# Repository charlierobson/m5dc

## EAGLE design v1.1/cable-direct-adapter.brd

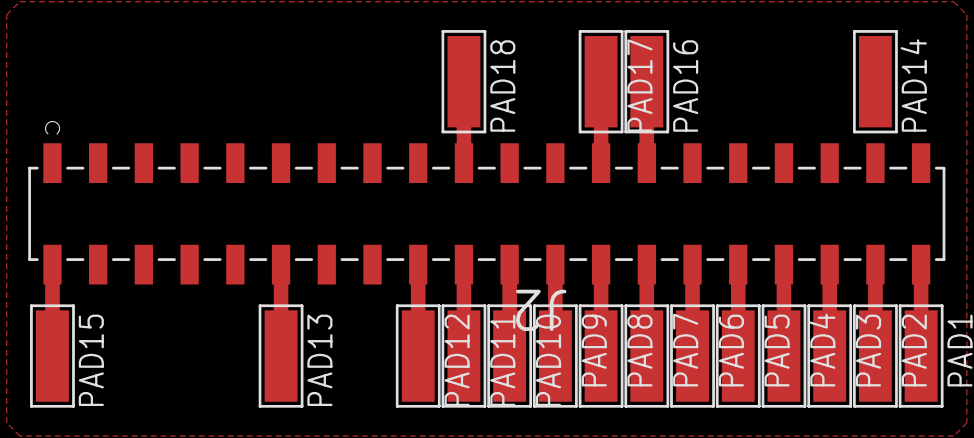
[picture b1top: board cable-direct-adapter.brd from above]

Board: 2 copper layers, 19 parts (0 on the bottom side), 18 nets.

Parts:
J2: SSM-120-L-DV; SAMTEC_SSM-120-L-DV
PAD1, PAD2, PAD3, PAD4, PAD5, PAD6, PAD7, PAD8, PAD9, PAD10, PAD11, PAD12, PAD13, PAD14, PAD15, PAD16, PAD17, PAD18: WIREPADSMD5-1,8; 5-1,8

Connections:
!IN: J2.19, PAD18.1
!OUT: J2.12, PAD13.1
!RESET: J2.2, PAD15.1
A0: J2.25, PAD17.1
A1: J2.27, PAD16.1
A2: J2.40, PAD1.1
A3: J2.34, PAD4.1
A6: J2.38, PAD2.1
A7: J2.36, PAD3.1
D0: J2.30, PAD6.1
D1: J2.22, PAD10.1
D2: J2.32, PAD5.1
D3: J2.26, PAD8.1
D4: J2.18, PAD12.1
D5: J2.28, PAD7.1
D6: J2.24, PAD9.1
D7: J2.20, PAD11.1
GND: J2.8, J2.29, J2.37, PAD14.1

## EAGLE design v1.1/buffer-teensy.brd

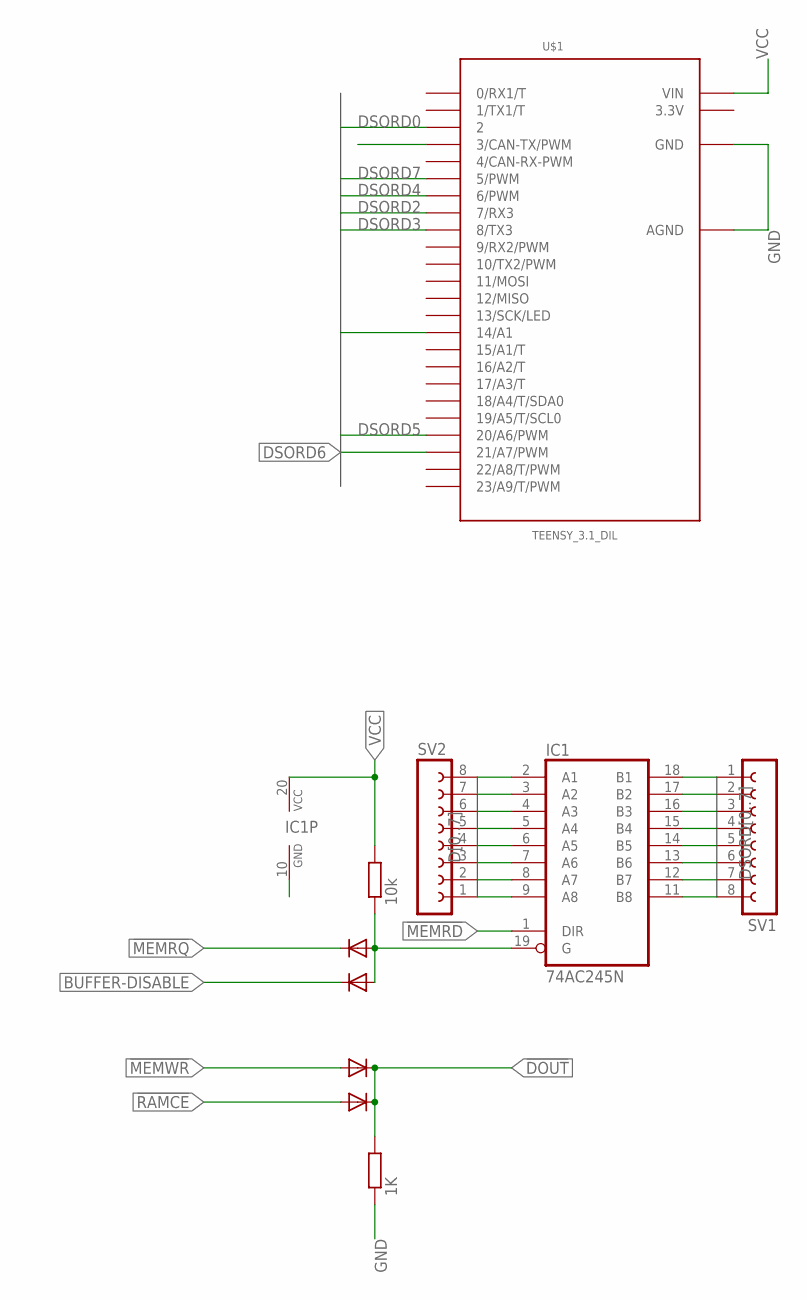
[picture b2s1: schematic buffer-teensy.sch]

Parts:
D1, D2, D3, D4: 1N4148DO35-7; DO35-7
IC1: 74AC245N; DIL20
R1: 10k; 0204/7
R2: 1K; 0204/7
SV1, SV2: FE08-1; FE08
U$1: TEENSY_3.1_DIL; TEENSY3-DIL

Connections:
3.3V: U$1.3.3V
!DOUT: D3.C, D4.C, R2.2, U$1.3 (3/CAN-TX/PWM)
!MEMRD: IC1.1 (DIR)
!MEMRQ: D1.C
!MEMWR: D3.A
!RAMCE: D4.A
BUFFER-DISABLE: D2.C
D0: IC1.2 (A1), SV2.8
D1: IC1.3 (A2), SV2.7
D2: IC1.4 (A3), SV2.6
D3: IC1.5 (A4), SV2.5
D4: IC1.6 (A5), SV2.4
D5: IC1.7 (A6), SV2.3
D6: IC1.8 (A7), SV2.2
D7: IC1.9 (A8), SV2.1
DSORD0: IC1.18 (B1), SV1.1, U$1.2
DSORD1: IC1.17 (B2), SV1.2, U$1.14/A0 (14/A1)
DSORD2: IC1.16 (B3), SV1.3, U$1.7 (7/RX3)
DSORD3: IC1.15 (B4), SV1.4, U$1.8 (8/TX3)
DSORD4: IC1.14 (B5), SV1.5, U$1.6 (6/PWM)
DSORD5: IC1.13 (B6), SV1.6, U$1.20/A6 (20/A6/PWM)
DSORD6: IC1.12 (B7), SV1.7, U$1.21/A7 (21/A7/PWM)
DSORD7: IC1.11 (B8), SV1.8, U$1.5 (5/PWM)
GND: IC1.10 (GND), R2.1, U$1.AGND, U$1.GND
unnamed: D1.A, D2.A, IC1.19 (G), R1.1
VCC: IC1.20 (VCC), R1.2, U$1.VIN

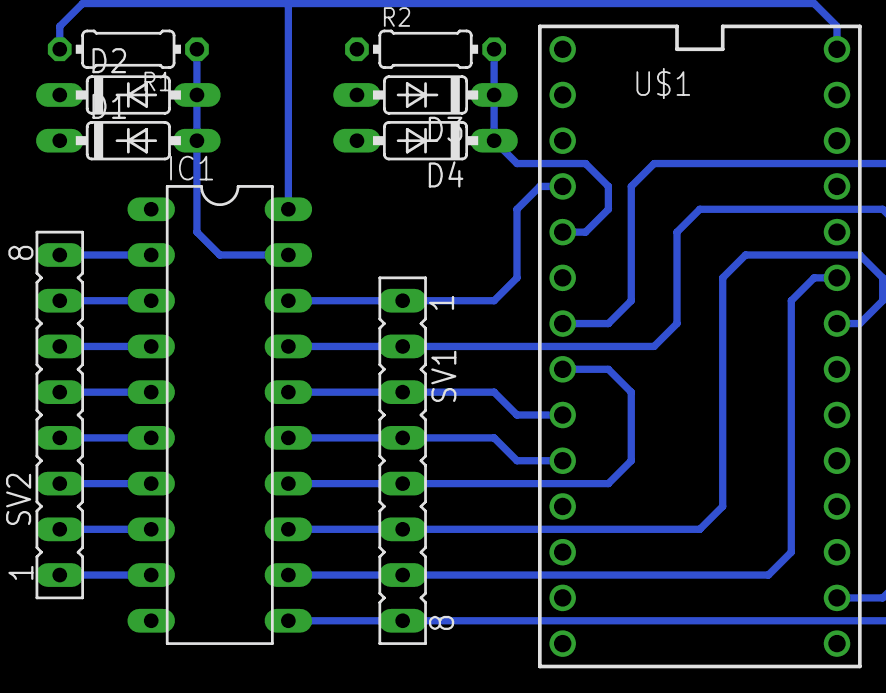
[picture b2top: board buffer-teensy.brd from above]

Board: 2 copper layers, 10 parts (0 on the bottom side), 20 nets.

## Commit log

2016-09-30 create new repo
2016-09-30 update test rom to load a file from an einsdein
2016-09-30 add direct adapter
2016-10-01 add xilinx code and finish direct adapter
2016-10-03 add new functinos to test rom
2016-10-03 add test mode
2016-10-04 add pic code to project
2016-10-04 add cpld and update rom to be mostly working
2016-10-04 update tasks to be mac compatible - but still not working - and adding crc calculator to pic
2016-10-04 add crc output to disk read
2016-10-04 get a little closer
2016-10-04 add tools to loader
2016-10-04 get loading working! still doesn't execute tho ...
2016-10-04 extend usability a bit
2016-10-04 add test2 rom, which loads the main program into ram
2016-10-05 rework build and rename source files to be less ... testy
2016-10-05 tidy up the code and add a default binary for when einsdein is not found
2016-10-05 add e000 code for mem upload test
2016-10-05 remove genie bodge that kills 1st 6 bytes :(
2016-10-06 remove all PC based print functions
2016-10-06 make things work! v1.0 working, but care needs to be taken over integration
2016-10-06 clean up after internet blackout yikes
2016-10-06 reshuffle working folder to enable sharing of commandIDs file after updating pic core, adding read checksum capabilities
2016-10-06 change DIR code to be less machine specific
2016-10-06 ensure memory usage isn't overlapping by removing magic numbers
2016-10-07 add file end detection, upgrade ROM bootloader
2016-10-07 tidy up code for release
2016-10-07 add code to do loading from dir list
